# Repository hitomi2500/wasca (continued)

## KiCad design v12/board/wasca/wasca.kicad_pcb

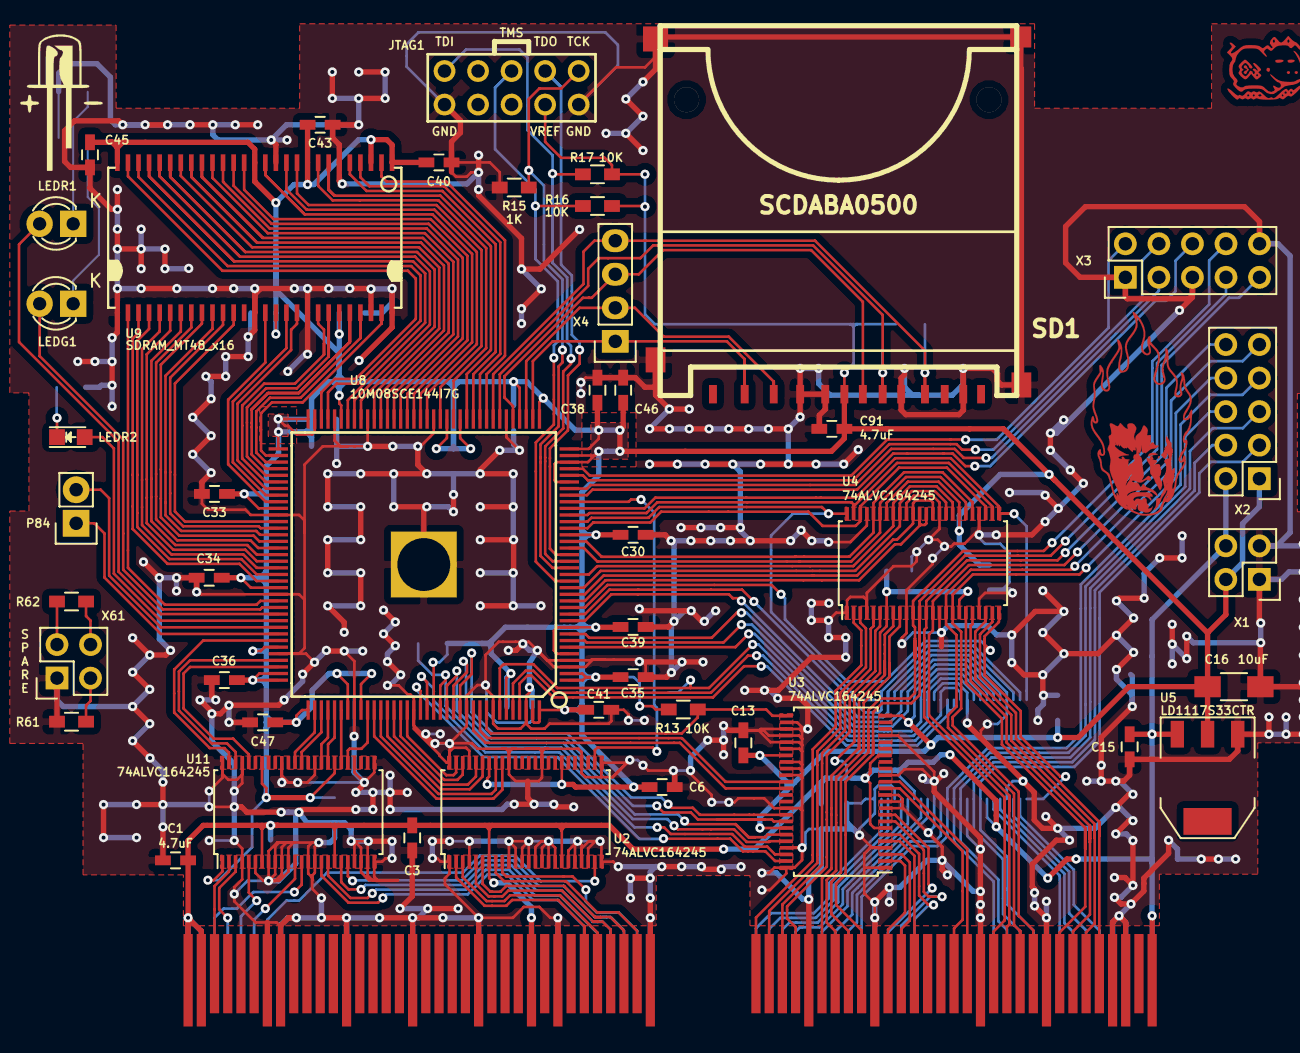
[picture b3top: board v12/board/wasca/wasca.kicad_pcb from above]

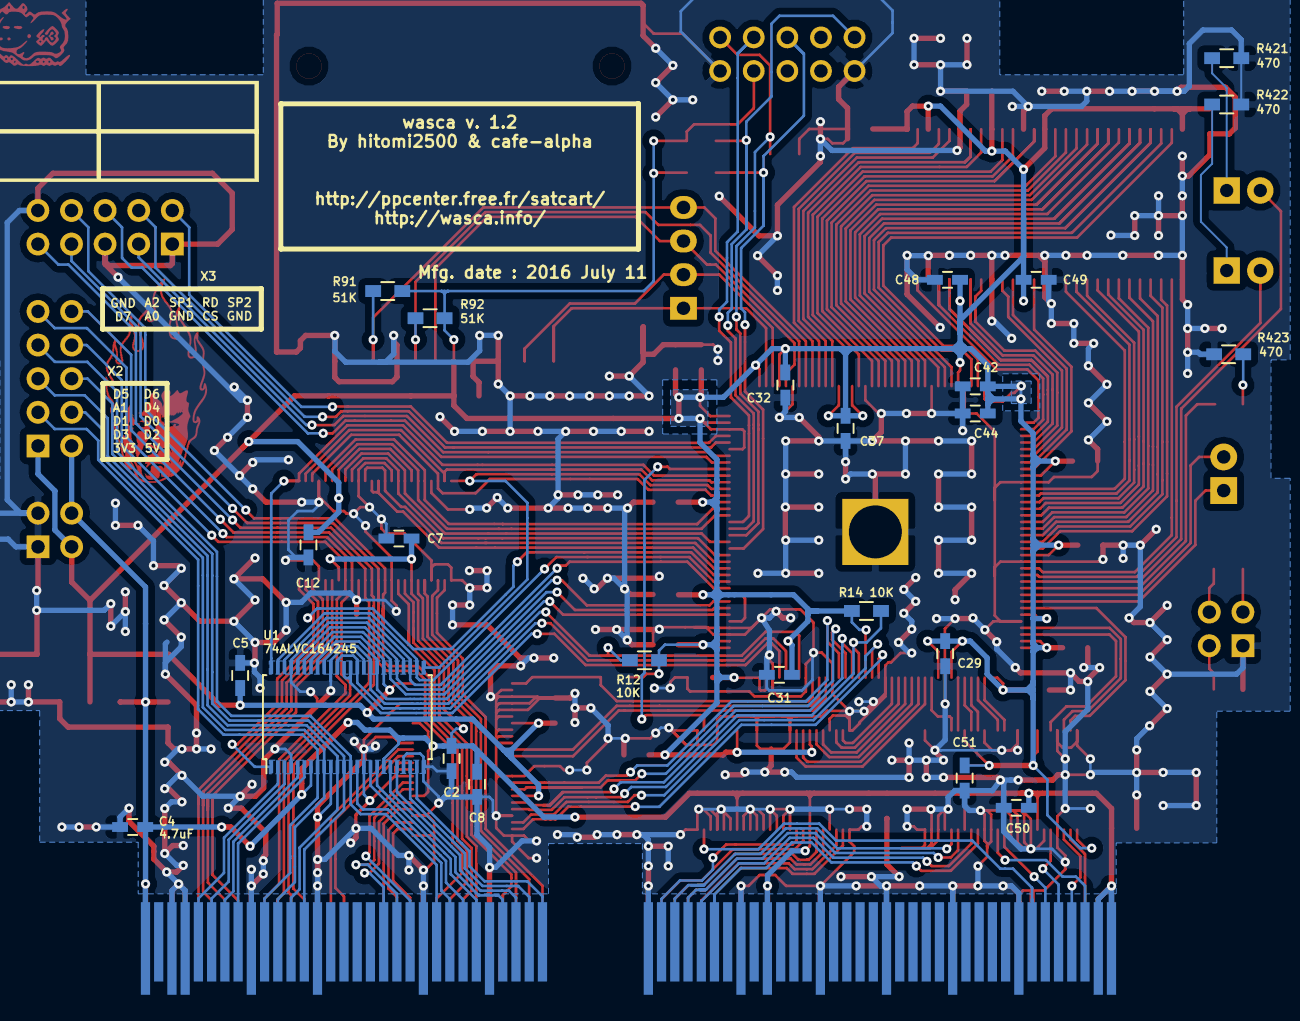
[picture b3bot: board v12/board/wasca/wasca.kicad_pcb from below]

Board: 2 copper layers, 69 parts (24 on the bottom side), 166 nets.

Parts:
C1, C4, C91: 4.7uF; C_0603_HandSoldering
C2, C3, C5, C6, C7, C8, C12, C13, C15, C29, C30, C31, C32, C33, C34, C35, C36, C37, C38, C39, C40, C41, C42, C43, C44, C45, C46, C47, C48, C49, C50, C51: 0.1uF; C_0603_HandSoldering
C16: 10uF; C_1206_HandSoldering
CN1: CARTRIDGE_EDGE_CONNECTOR; CARTRIDGE_EDGE_CONNECTOR2
JTAG1: AVR-JTAG-10; JTAG_Header
LEDG1: LED; LED-3MM
LEDR1: LED; LED-3MM
LEDR2: LED; LED_0805
P84: CONN_01X02; Pin_Header_Straight_1x02
R12, R13, R14, R16, R17: 10K; R_0603_HandSoldering
R15, R61, R62: 1K; R_0603_HandSoldering
R91, R92: 51K; R_0603_HandSoldering
R421, R422, R423: 470; R_0603_HandSoldering
SD1: SD_CARD; sd_socket
U1, U2, U3, U4, U11: 74ALVC164245; TSSOP-48_6.1x12.5mm_Pitch0.5mm
U5: LD1117S33CTR; SOT-223
U8: 10M08SCE144I7G; TQFP144_ALTERA_HANDSOLDERING
U9: SDRAM_MT48_x16; TSOPII54_SDRAM_MT48
X1, X61: CONN_02X02; Pin_Header_Straight_2x02
X2, X3: CONN_02X05; Pin_Header_Straight_2x05
X4: CONN_01X04; Pin_Header_Straight_1x04

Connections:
/+3_3V: C5.1, C6.1, C12.1, C13.1, C16.1, C29.1, C30.1, C31.1, C32.1, C33.1, C34.1, C35.1, C36.1, C37.1, C38.1, C39.1, C40.1, C41.1, C42.1, C43.1, C44.1, C45.1, C46.1, C47.1, C48.1, C49.1, C51.1, C91.1, JTAG1.4, R12.1, R13.1, R14.1, R16.1, R17.1, R91.1, R92.1, SD1.4, U1.31, U1.42, U2.31, U2.42, U3.24, U3.31, U3.42, U4.31, U4.42, U5.2, U8.1, U8.2, U8.5, U8.9, U8.23, U8.31, U8.34, U8.35, U8.36, U8.37, U8.40, U8.49, U8.51, U8.67, U8.71, U8.72, U8.73, U8.82, U8.94, U8.103, U8.107, U8.108, U8.109, U8.115, U8.117, U8.128, U8.139, U8.143, U8.144, U9.1, U9.3, U9.9, U9.14, U9.27, U9.43, U9.49, U11.1, U11.31, U11.42, X1.2, X2.1
/+5V: C1.1, C2.1, C3.1, C4.1, C7.1, C8.1, C15.1, C50.1, CN1.A1, CN1.A2, CN1.A27, CN1.A67, CN1.B1, CN1.B2, CN1.B27, CN1.B67, U1.7, U1.18, U2.7, U2.18, U3.7, U3.18, U4.7, U4.18, U5.3, U11.7, U11.18, X1.4, X2.2
/ABUS_3V_A16: U2.41, U8.120
/ABUS_3V_A17: U2.40, U8.119
/ABUS_3V_A18: U2.43, U8.121
/ABUS_3V_A19: U8.118, U11.29
/ABUS_3V_A20: U2.44, U8.122
/ABUS_3V_A21: U8.114, U11.30
/ABUS_3V_A22: U2.46, U8.123
/ABUS_3V_A23: U8.113, U11.32
/ABUS_3V_A24: U2.47, U8.124
/ABUS_3V_A25: U8.112, U11.33
/ABUS_3V_CS0: U3.40, U8.132
/ABUS_3V_CS1: U3.46, U8.127
/ABUS_3V_CS2: U3.41, U8.131
/ABUS_3V_IRQ: U3.35, U8.135
/ABUS_3V_MUX0: U1.36, U1.37, U8.141
/ABUS_3V_MUX1: U1.35, U1.38, U8.140
/ABUS_3V_MUX2: R12.2, U1.33, U1.40, U8.138
/ABUS_3V_MUX3: U1.32, U1.41, U8.6
/ABUS_3V_MUX4: U4.32, U4.41, U8.17
/ABUS_3V_MUX5: U4.33, U4.40, U8.15
/ABUS_3V_MUX6: U4.35, U4.38, U8.14
/ABUS_3V_MUX7: U4.36, U4.37, U8.13
/ABUS_3V_MUX8: U1.30, U1.43, U8.7
/ABUS_3V_MUX9: U1.29, U1.44, U8.8
/ABUS_3V_MUX10: U1.27, U1.46, U8.10
/ABUS_3V_MUX11: U1.26, U1.47, U8.11
/ABUS_3V_MUX12: U4.26, U4.47, U8.26
/ABUS_3V_MUX13: U4.27, U4.46, U8.24
/ABUS_3V_MUX14: U4.29, U4.44, U8.22
/ABUS_3V_MUX15: U4.30, U4.43, U8.21
/ABUS_3V_MUX_DATA_DIR: U1.1, U4.24, U8.12
/ABUS_3V_MUX_EN1: U1.25, U4.48, U8.25
/ABUS_3V_MUX_EN2: U1.48, U4.25, U8.27
/ABUS_3V_RD: U3.47, U8.126
/ABUS_3V_WAIT: U3.36, U8.134
/ABUS_3V_WR0: U3.43, U8.130
/ABUS_3V_WR1: R14.2, U3.44, U8.129
/ABUS_A0: CN1.B45, U4.12, X3.7
/ABUS_A1: CN1.A45, U1.13, X2.7
/ABUS_A2: CN1.B44, U4.11, X3.8
/ABUS_A3: CN1.B43, U4.9
/ABUS_A4: CN1.B42, U4.8
/ABUS_A5: CN1.B40, U4.6
/ABUS_A6: CN1.B39, U4.5
/ABUS_A7: CN1.B38, U4.3
/ABUS_A8: CN1.A40, U1.19
/ABUS_A9: CN1.A42, U1.17
/ABUS_A10: CN1.A44, U1.14
/ABUS_A11: CN1.A43, U1.16
/ABUS_A12: CN1.A38, U1.22
/ABUS_A13: CN1.A39, U1.20
/ABUS_A14: CN1.B37, U4.2
/ABUS_A15: CN1.A37, U1.23
/ABUS_A16: CN1.B35, U2.8
/ABUS_A17: CN1.A35, U2.9
/ABUS_A18: CN1.B34, U2.6
/ABUS_A19: CN1.A34, U11.20
/ABUS_A20: CN1.B33, U2.5
/ABUS_A21: CN1.A33, U11.19
/ABUS_A22: CN1.B32, U2.3
/ABUS_A23: CN1.A32, U11.17
/ABUS_A24: CN1.B31, U2.2
/ABUS_A25: CN1.A31, U11.16
/ABUS_CS0: CN1.A47, U3.9
/ABUS_CS1: CN1.B48, U3.3
/ABUS_CS2: CN1.A48, U3.8
/ABUS_D0: CN1.A55, U1.12, X2.6
/ABUS_D1: CN1.A56, U1.11, X2.5
/ABUS_D2: CN1.A57, U1.9, X2.4
/ABUS_D3: CN1.A58, U1.8, X2.3
/ABUS_D4: CN1.B58, U4.17, X2.8
/ABUS_D5: CN1.B57, U4.16, X2.9
/ABUS_D6: CN1.B56, U4.14, X2.10
/ABUS_D7: CN1.B55, U4.13, X3.9
/ABUS_D8: CN1.A60, U1.6
/ABUS_D9: CN1.A61, U1.5
/ABUS_D10: CN1.A62, U1.3
/ABUS_D11: CN1.A63, U1.2
/ABUS_D12: CN1.B63, U4.23
/ABUS_D13: CN1.B62, U4.22
/ABUS_D14: CN1.B61, U4.20
/ABUS_D15: CN1.B60, U4.19
/ABUS_IRQ: CN1.B53, U3.14
/ABUS_RD: CN1.B47, U3.2
/ABUS_WAIT: CN1.B52, U3.13
/ABUS_WR0: CN1.A49, U3.6
/ABUS_WR1: CN1.B49, U3.5
/DDR_SPARE1: LEDR2.2, U8.99
/DDR_SPARE2: P84.2, U8.100
/DDR_SPARE3: P84.1, U8.101
/IBCK: CN1.A5, U11.5
/IBCK_3V: U8.106, U11.44
/ILRCK: CN1.A6, U11.12
/ILRCK_3V: U8.110, U11.37
/ISD: CN1.A4, U11.3
/ISD_3V: U8.105, U11.46
/JTAG_TCK: JTAG1.1, R15.1, U8.18
/JTAG_TDI: JTAG1.9, R17.2, U8.19
/JTAG_TDO: JTAG1.3, U8.20
/JTAG_TMS: JTAG1.5, R16.2, U8.16
/LEDG1: LEDG1.2, U8.97
/LEDR1: LEDR1.2, U8.98
/RESET: CN1.A3, U11.13
/RESET_3V: U8.111, U11.36
/SCSPCLK: CN1.A7, U2.23
/SCSPCLK_3V: U2.26, U8.28
/SDR_A0: U8.65, U9.23
/SDR_A1: U8.66, U9.24
/SDR_A2: U8.69, U9.25
/SDR_A3: U8.70, U9.26
/SDR_A4: U8.96, U9.29
/SDR_A5: U8.93, U9.30
/SDR_A6: U8.92, U9.31
/SDR_A7: U8.91, U9.32
/SDR_A8: U8.90, U9.33
/SDR_A9: U8.89, U9.34
/SDR_A10: U8.64, U9.22
/SDR_A11: U8.88, U9.35
/SDR_A12: U8.87, U9.36
/SDR_BA0: U8.61, U9.20
/SDR_BA1: U8.62, U9.21
/SDR_CAS: U8.58, U9.17
/SDR_CKE: U8.86, U9.37
/SDR_CLK: U8.85, U9.38
/SDR_CS: U8.60, U9.19
/SDR_DQ0: U8.45, U9.2
/SDR_DQ1: U8.46, U9.4
/SDR_DQ2: U8.47, U9.5
/SDR_DQ3: U8.48, U9.7
/SDR_DQ4: U8.50, U9.8
/SDR_DQ5: U8.52, U9.10
/SDR_DQ6: U8.54, U9.11
/SDR_DQ7: U8.55, U9.13
/SDR_DQ8: U8.81, U9.42
/SDR_DQ9: U8.80, U9.44
/SDR_DQ10: U8.79, U9.45
/SDR_DQ11: U8.78, U9.47
/SDR_DQ12: U8.77, U9.48
/SDR_DQ13: U8.76, U9.50
/SDR_DQ14: U8.75, U9.51
/SDR_DQ15: U8.74, U9.53
/SDR_DQMH: U8.84, U9.39
/SDR_DQML: U8.56, U9.15
/SDR_RAS: U8.59, U9.18
/SDR_WE: U8.57, U9.16
/SD_CLK: SD1.5, U8.41, X4.3
/SD_CS: SD1.1, U8.38, X4.1
/SD_DIN: SD1.2, U8.39, X4.2
/SD_DOUT: R91.2, SD1.7, U8.44, X4.4
/SSEL: CN1.B3, U11.2
/SSEL_3V: U8.102, U11.47
/USB_CS: U8.30, X3.3
/USB_RD: U8.32, X3.4
/USB_SPARE1: U8.29, X3.6
/USB_SPARE2: U8.33, X3.2
/WAIT_ENABLE: R13.2, U3.25, U8.136
GND: C1.2, C2.2, C3.2, C4.2, C5.2, C6.2, C7.2, C8.2, C12.2, C13.2, C15.2, C16.2, C29.2, C30.2, C31.2, C32.2, C33.2, C34.2, C35.2, C36.2, C37.2, C38.2, C39.2, C40.2, C41.2, C42.2, C43.2, C44.2, C45.2, C46.2, C47.2, C48.2, C49.2, C50.2, C51.2, C91.2, CN1.A8, CN1.A13, CN1.A18, CN1.A23, CN1.A29, CN1.A36, CN1.A41, CN1.A46, CN1.A54, CN1.A59, CN1.A64, CN1.A65, CN1.B7, CN1.B8, CN1.B13, CN1.B18, CN1.B23, CN1.B29, CN1.B36, CN1.B41, CN1.B46, CN1.B54, CN1.B59, CN1.B64, CN1.B65, JTAG1.2, JTAG1.10, R15.2, R61.1, R421.2, R422.2, R423.2, SD1.3, SD1.6, SD1.12, SD1.13, SD1.14, SD1.15, SD1.16, SD1.17, U1.4, U1.10, U1.15, U1.21, U1.24, U1.28, U1.34, U1.39, U1.45, U2.1, U2.4, U2.10, U2.11, U2.12, U2.13, U2.14, U2.15, U2.16, U2.17, U2.19, U2.20, U2.21, U2.22, U2.24, U2.25, U2.28, U2.34, U2.39, U2.45, U2.48, U3.1, U3.4, U3.10, U3.11, U3.12, U3.15, U3.21, U3.26, U3.27, U3.28, U3.29, U3.30, U3.32, U3.33, U3.34, U3.39, U3.45, U3.48, U4.1, U4.4, U4.10, U4.15, U4.21, U4.28, U4.34, U4.39, U4.45, U5.1, U8.3, U8.4, U8.42, U8.53, U8.63, U8.68, U8.83, U8.95, U8.104, U8.116, U8.125, U8.133, U8.137, U8.142, U8.145, U9.6, U9.12, U9.28, U9.41, U9.46, U9.52, U9.54, U11.4, U11.6, U11.8, U11.9, U11.10, U11.11, U11.14, U11.15, U11.21, U11.22, U11.23, U11.24, U11.25, U11.28, U11.34, U11.39, U11.45, U11.48, X1.1, X1.3, X3.1, X3.5, X3.10, X61.1
unnamed: LEDG1.1, R422.1
unnamed: LEDR1.1, R421.1
unnamed: LEDR2.1, R423.1
unnamed: R61.2, X61.3
unnamed: R62.1, X61.2
unnamed: R62.2, X61.4
unnamed: R92.2, SD1.10, U8.43

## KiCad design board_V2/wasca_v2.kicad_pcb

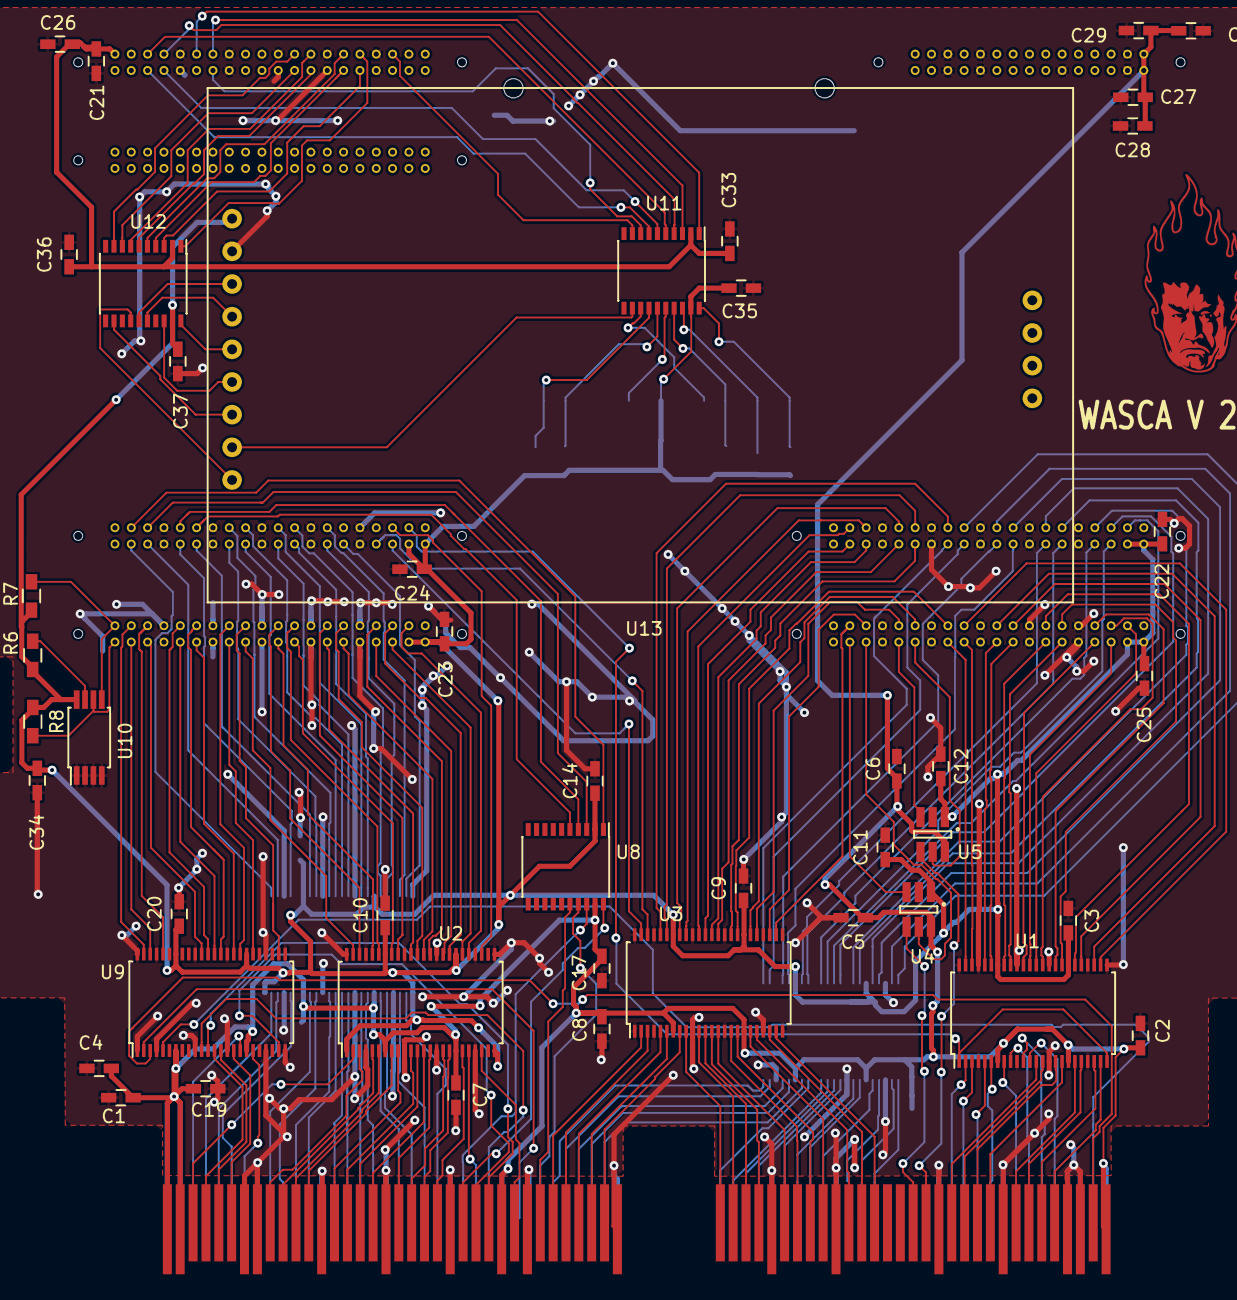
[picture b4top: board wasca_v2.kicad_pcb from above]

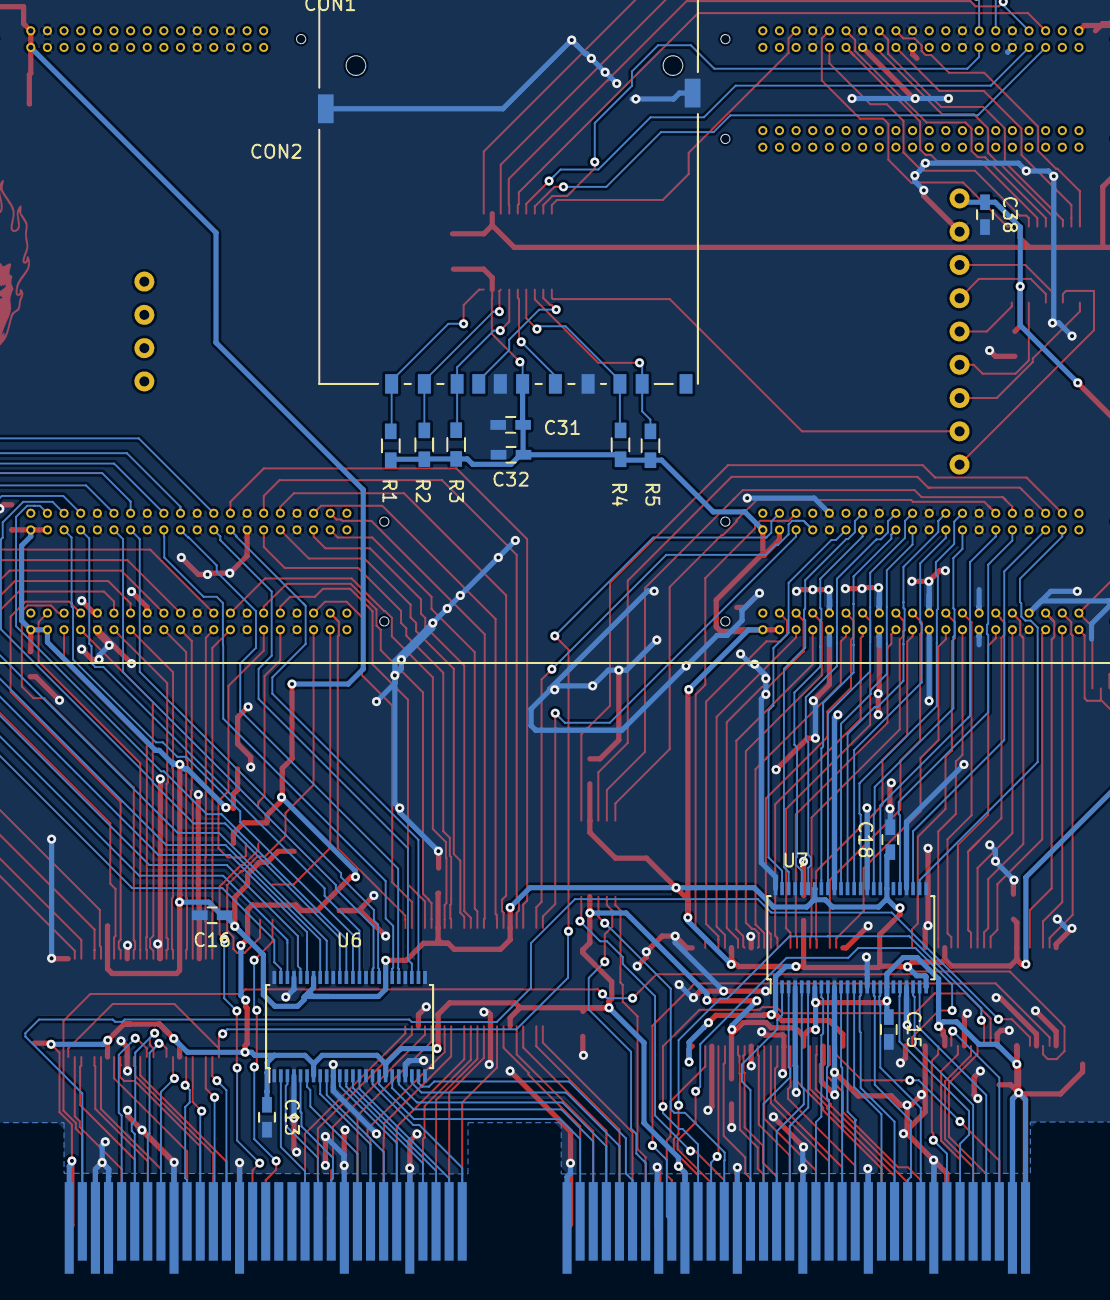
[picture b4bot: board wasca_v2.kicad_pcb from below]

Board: 2 copper layers, 62 parts (16 on the bottom side), 230 nets.

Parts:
C1, C26, C28, C30: 10uF; C_0603_HandSoldering
C2, C3, C4, C5, C6, C7, C8, C9, C10, C11, C12, C13, C14, C15, C16, C17, C18, C19, C20, C21, C22, C23, C24, C25, C27, C29, C32, C33, C34, C35, C36, C37, C38: 0.1uF; C_0603_HandSoldering
C31: 1uF; C_0603_HandSoldering
CN1: CARTRIDGE_EDGE_CONNECTOR; CARTRIDGE_EDGE_CONNECTOR2
CON1: SnickerDoodle
CON2: SD_Card; SD_Card_Receptacle
R1, R2, R3, R4, R5: 50K; R_0603_HandSoldering
R6: 0; R_0603_HandSoldering
R7, R8: 10K; R_0603_HandSoldering
U1, U2, U3, U6, U7, U9: 74ALVC164245; TSSOP-48_6.1x12.5mm_Pitch0.5mm
U4, U5: 74LVC1T45GW,125; SOT-23-6_Handsoldering
U8, U11, U12: TXS0108EPWR; SSOP-20_4.4x6.5mm_Pitch0.65mm
U10: M24C04-WDW6TP; TSSOP-8_4.4x3mm_Pitch0.65mm
U13: ILI9341_LCD_Breakout

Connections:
/+1_8V: C21.1, C26.1, C33.1, C36.1, CON1.B1, U11.2, U12.2
/+3_3V: C3.1, C9.1, C10.1, C11.1, C12.1, C14.1, C16.1, C18.1, C20.1, C22.1, C23.1, C24.1, C25.1, C31.1, C32.1, C34.1, C35.1, C37.1, C38.1, CON1.C1, CON1.C3, CON1.D1, CON1.D3, CON1.E1, CON1.E3, CON1.F1, CON1.F3, CON2.4, R1.1, R2.1, R3.1, R4.1, R5.1, R6.1, R7.1, R8.1, U1.31, U1.42, U2.1, U2.24, U2.31, U2.42, U3.31, U3.42, U4.1, U5.1, U6.31, U6.42, U7.1, U7.24, U7.31, U7.42, U8.2, U9.31, U9.42, U10.8, U11.19, U12.19, U13.1
/+5V: C1.1, C2.1, C4.1, C5.1, C6.1, C7.1, C8.1, C13.1, C15.1, C17.1, C19.1, C27.1, C28.1, C29.1, C30.1, CN1.A1, CN1.A2, CN1.A27, CN1.A67, CN1.B1, CN1.B2, CN1.B27, CN1.B67, CON1.A29, CON1.A30, U1.7, U1.18, U2.7, U2.18, U3.7, U3.18, U4.6, U5.6, U6.7, U6.18, U7.7, U7.18, U8.19, U9.7, U9.18
/ABUS_A0: CN1.B45, U3.19
/ABUS_A0_3V: CON1.E30, U3.30
/ABUS_A1: CN1.A45, U6.6
/ABUS_A1_3V: CON1.F14, U6.43
/ABUS_A2: CN1.B44, U3.17
/ABUS_A2_3V: CON1.E26, U3.32
/ABUS_A3: CN1.B43, U3.16
/ABUS_A3_3V: CON1.F29, U3.33
/ABUS_A4: CN1.B42, U3.14
/ABUS_A4_3V: CON1.F31, U3.35
/ABUS_A5: CN1.B40, U3.13
/ABUS_A5_3V: CON1.F35, U3.36
/ABUS_A6: CN1.B39, U3.12
/ABUS_A6_3V: CON1.F37, U3.37
/ABUS_A7: CN1.B38, U3.11
/ABUS_A7_3V: CON1.F38, U3.38
/ABUS_A8: CN1.A40, U6.12
/ABUS_A8_3V: CON1.F4, U6.37
/ABUS_A9: CN1.A42, U6.11
/ABUS_A9_3V: CON1.F6, U6.38
/ABUS_A10: CN1.A44, U6.8
/ABUS_A10_3V: CON1.F12, U6.41
/ABUS_A11: CN1.A43, U6.9
/ABUS_A11_3V: CON1.F8, U6.40
/ABUS_A12: CN1.A38, U6.14
/ABUS_A12_3V: CON1.F7, U6.35
/ABUS_A13: CN1.A39, U6.13
/ABUS_A13_3V: CON1.F5, U6.36
/ABUS_A14: CN1.B37, U3.9
/ABUS_A14_3V: CON1.F36, U3.40
/ABUS_A15: CN1.A37, U6.16
/ABUS_A15_3V: CON1.F11, U6.33
/ABUS_A16: CN1.B35, U3.8
/ABUS_A16_3V: CON1.F32, U3.41
/ABUS_A17: CN1.A35, U6.17
/ABUS_A17_3V: CON1.F13, U6.32
/ABUS_A18: CN1.B34, U3.6
/ABUS_A18_3V: CON1.F30, U3.43
/ABUS_A19: CN1.A34, U6.19
/ABUS_A19_3V: CON1.F17, U6.30
/ABUS_A20: CN1.B33, U3.5
/ABUS_A20_3V: CON1.F26, U3.44
/ABUS_A21: CN1.A33, U6.20
/ABUS_A21_3V: CON1.F19, U6.29
/ABUS_A22: CN1.B32, U3.3
/ABUS_A22_3V: CON1.D7, U3.46
/ABUS_A23: CN1.A32, U6.22
/ABUS_A23_3V: CON1.F23, U6.27
/ABUS_A24: CN1.B31, U3.2
/ABUS_A24_3V: CON1.D5, U3.47
/ABUS_A25: CN1.A31, U6.23
/ABUS_A25_3V: CON1.F25, U6.26
/ABUS_CS0: CN1.A47, U6.5
/ABUS_CS0_3V: CON1.F18, U6.44
/ABUS_CS1: CN1.B48, U3.22
/ABUS_CS1_3V: CON1.E36, U3.27
/ABUS_CS2: CN1.A48, U6.3
/ABUS_CS2_3V: CON1.F20, U6.46
/ABUS_D0: CN1.A55, U1.2
/ABUS_D0_3V: CON1.E25, U1.47
/ABUS_D1: CN1.A56, U1.3
/ABUS_D1_3V: CON1.E23, U1.46
/ABUS_D2: CN1.A57, U1.5
/ABUS_D2_3V: CON1.E19, U1.44
/ABUS_D3: CN1.A58, U1.6
/ABUS_D3_3V: CON1.E17, U1.43
/ABUS_D4: CN1.B58, U1.17
/ABUS_D4_3V: CON1.E12, U1.32
/ABUS_D5: CN1.B57, U1.16
/ABUS_D5_3V: CON1.E8, U1.33
/ABUS_D6: CN1.B56, U1.14
/ABUS_D6_3V: CON1.E6, U1.35
/ABUS_D7: CN1.B55, U1.13
/ABUS_D7_3V: CON1.E4, U1.36
/ABUS_D8: CN1.A60, U1.8
/ABUS_D8_3V: CON1.E13, U1.41
/ABUS_D9: CN1.A61, U1.9
/ABUS_D9_3V: CON1.E11, U1.40
/ABUS_D10: CN1.A62, U1.11
/ABUS_D10_3V: CON1.E7, U1.38
/ABUS_D11: CN1.A63, U1.12
/ABUS_D11_3V: CON1.E5, U1.37
/ABUS_D12: CN1.B63, U1.23
/ABUS_D12_3V: CON1.E24, U1.26
/ABUS_D13: CN1.B62, U1.22
/ABUS_D13_3V: CON1.E20, U1.27
/ABUS_D14: CN1.B61, U1.20
/ABUS_D14_3V: CON1.E18, U1.29
/ABUS_D15: CN1.B60, U1.19
/ABUS_D15_3V: CON1.E14, U1.30
/ABUS_DATA_DIR: CON1.D4, U1.1, U1.24
/ABUS_IRQ: CN1.B53, U5.4
/ABUS_IRQ_3V: CON1.E31, U5.3
/ABUS_IRQ_DIR: CON1.E29, U5.5
/ABUS_RD: CN1.B47, U3.20
/ABUS_RD_3V: CON1.E32, U3.29
/ABUS_WAIT: CN1.B52, U4.4
/ABUS_WAIT_3V: CON1.E37, U4.3
/ABUS_WAIT_DIR: CON1.E35, U4.5
/ABUS_WR0: CN1.A49, U6.2
/ABUS_WR0_3V: CON1.F24, U6.47
/ABUS_WR1: CN1.B49, U3.23
/ABUS_WR1_3V: CON1.E38, U3.26
/COPRO_RST: CN1.A66, U9.5
/COPRO_RST_3V: CON1.C36, U9.44
/CRTG0: CN1.A30, U8.17
/CRTG0_3V: CON1.D32, U8.4
/CRTG1: CN1.B30, U8.16
/CRTG1_3V: CON1.D30, U8.5
/DBCK: CN1.B5, U9.14
/DBCK_3V: CON1.C30, U9.35
/DLRCLK: CN1.B6, U9.16
/DLRCLK_3V: CON1.C29, U9.33
/DOTCLK: CN1.A28, U9.2
/DOTCLK_3V: CON1.C38, U9.47
/DSD: CN1.B4, U9.13
/DSD_3V: CON1.C31, U9.36
/EXBG0: CN1.A9, U7.17
/EXBG0_3V: CON1.D29, U7.32
/EXBG1: CN1.B9, U2.3
/EXBG1_3V: CON1.C20, U2.46
/EXBG2: CN1.A10, U7.16
/EXBG2_3V: CON1.D25, U7.33
/EXBG3: CN1.B10, U2.5
/EXBG3_3V: CON1.C19, U2.44
/EXBG4: CN1.A11, U7.14
/EXBG4_3V: CON1.D26, U7.35
/EXBG5: CN1.B11, U2.6
/EXBG5_3V: CON1.C18, U2.43
/EXBG6: CN1.A12, U7.13
/EXBG6_3V: CON1.D23, U7.36
/EXBG7: CN1.B12, U2.8
/EXBG7_3V: CON1.C17, U2.41
/EXBG8: CN1.A14, U7.12
/EXBG8_3V: CON1.D24, U7.37
/EXBG9: CN1.B14, U2.9
/EXBG9_3V: CON1.C14, U2.40
/EXBG10: CN1.A15, U7.11
/EXBG10_3V: CON1.D19, U7.38
/EXBG11: CN1.B15, U2.11
/EXBG11_3V: CON1.C13, U2.38
/EXBG12: CN1.A16, U7.9
/EXBG12_3V: CON1.D20, U7.40
/EXBG13: CN1.B16, U2.12
/EXBG13_3V: CON1.C12, U2.37
/EXBG14: CN1.A17, U7.8
/EXBG14_3V: CON1.D17, U7.41
/EXBG15: CN1.B17, U2.13
/EXBG15_3V: CON1.C11, U2.36
/EXBG16: CN1.A19, U7.6
/EXBG16_3V: CON1.D18, U7.43
/EXBG17: CN1.B19, U2.14
/EXBG17_3V: CON1.C8, U2.35
/EXBG18: CN1.A20, U7.5
/EXBG18_3V: CON1.D13, U7.44
/EXBG19: CN1.B20, U2.16
/EXBG19_3V: CON1.C7, U2.33
/EXBG20: CN1.A21, U7.3
/EXBG20_3V: CON1.D14, U7.46
/EXBG21: CN1.B21, U2.17
/EXBG21_3V: CON1.C6, U2.32
/EXBG22: CN1.A22, U7.2
/EXBG22_3V: CON1.D11, U7.47
/EXBG23: CN1.B22, U2.19
/EXBG23_3V: CON1.C5, U2.30
/EXLAT: CN1.A25, U2.20
/EXLAT_3V: CON1.C4, U2.29
/EXON: CN1.A24, U8.18
/EXON_3V: CON1.D36, U8.3
/EXSL: CN1.B25, U9.23
/EXSL_3V: CON1.C24, U9.26
/EXSYNC: CN1.B28, U2.22
/EXSYNC_3V: CON1.D6, U2.27
/HSYNC: CN1.A26, U9.11
/HSYNC_3V: CON1.C35, U9.38
/IBCK: CN1.A5, U7.22
/IBCK_3V: CON1.D35, U7.27
/ILRCK: CN1.A6, U7.20
/ILRCK_3V: CON1.D31, U7.29
/ISD: CN1.A4, U7.23
/ISD_3V: CON1.D37, U7.26
/LCD_DC: U12.20, U13.5
/LCD_DC_1_8V: CON1.B32, U12.3
/LCD_LED: U11.12, U13.8
/LCD_LED_1_8V: CON1.B35, U11.9
/LCD_RESET: U12.16, U13.4
/LCD_RESET_1_8V: CON1.B30, U12.4
/MCLK: CN1.B66, U9.3
/MCLK_3V: CON1.C37, U9.46
/MPEGON: CN1.B24, U8.20
/MPEGON_3V: CON1.D38, U8.1
/RESET: CN1.A3, U9.17
/RESET_3V: CON1.C26, U9.32
/SCSPCLK: CN1.A7, U9.19
/SCSPCLK_3V: CON1.C25, U9.30
/SD_CD/DAT3: CON2.1, R2.2, U11.18
/SD_CD/DAT3_1_8V: CON1.B13, U11.3
/SD_CLK: CON2.5, U11.16
/SD_CLK_1_8V: CON1.B5, U11.5
/SD_CMD: CON2.2, R3.2, U11.17
/SD_CMD_1_8V: CON1.B7, U11.4
/SD_DAT0: CON2.7, R4.2, U11.15
/SD_DAT0_1_8V: CON1.B8, U11.6
/SD_DAT1: CON2.8, R5.2, U11.14
/SD_DAT1_1_8V: CON1.B6, U11.7
/SD_DAT2: CON2.9, R1.2, U11.20
/SD_DAT2_1_8V: CON1.B11, U11.1
/SD_WP: CON2.10, U11.13
/SD_WP_1_8V: CON1.B14, U11.8
/SPI_CS0: U12.15, U13.3
/SPI_CS0_1_8V: CON1.B26, U12.6
/SPI_CS1_1_8V: CON1.B24, U12.8
/SPI_CS2_1_8V: CON1.B29, U12.5
/SPI_MISO: U12.14, U13.9
/SPI_MISO_1_8V: CON1.B25, U12.7
/SPI_MOSI: U12.18, U13.6
/SPI_MOSI_1_8V: CON1.B31, U12.1
/SPI_SCK: U12.12, U13.7
/SPI_SCK_1_8V: CON1.B23, U12.9
/SSEL: CN1.B3, U2.2
/SSEL_3V: CON1.C23, U2.47
/VSYNC: CN1.B26, U9.12
/VSYNC_3V: CON1.C32, U9.37
GND: C1.2, C2.2, C3.2, C4.2, C5.2, C6.2, C7.2, C8.2, C9.2, C10.2, C11.2, C12.2, C13.2, C14.2, C15.2, C16.2, C17.2, C18.2, C19.2, C20.2, C21.2, C22.2, C23.2, C24.2, C25.2, C26.2, C27.2, C28.2, C29.2, C30.2, C31.2, C32.2, C33.2, C34.2, C35.2, C36.2, C37.2, C38.2, CN1.A8, CN1.A13, CN1.A18, CN1.A23, CN1.A29, CN1.A36, CN1.A41, CN1.A46, CN1.A54, CN1.A59, CN1.A64, CN1.A65, CN1.B7, CN1.B8, CN1.B13, CN1.B18, CN1.B23, CN1.B29, CN1.B36, CN1.B41, CN1.B46, CN1.B54, CN1.B59, CN1.B64, CN1.B65, CON1.A5, CON1.A6, CON1.A9, CON1.A10, CON1.A20, CON1.A27, CON1.A28, CON1.B9, CON1.B10, CON1.B15, CON1.B16, CON1.B21, CON1.B22, CON1.B27, CON1.B28, CON1.B33, CON1.B34, CON1.C9, CON1.C10, CON1.C15, CON1.C16, CON1.C21, CON1.C22, CON1.C27, CON1.C28, CON1.C33, CON1.C34, CON1.D9, CON1.D10, CON1.D15, CON1.D16, CON1.D21, CON1.D22, CON1.D27, CON1.D28, CON1.D33, CON1.D34, CON1.E9, CON1.E10, CON1.E15, CON1.E16, CON1.E21, CON1.E22, CON1.E27, CON1.E28, CON1.E33, CON1.E34, CON1.F9, CON1.F10, CON1.F15, CON1.F16, CON1.F21, CON1.F22, CON1.F27, CON1.F28, CON1.F33, CON1.F34, CON2.3, CON2.6, CON2.12, CON2.13, U1.4, U1.10, U1.15, U1.21, U1.25, U1.28, U1.34, U1.39, U1.45, U1.48, U2.4, U2.10, U2.15, U2.21, U2.25, U2.28, U2.34, U2.39, U2.45, U2.48, U3.1, U3.4, U3.10, U3.15, U3.21, U3.24, U3.25, U3.28, U3.34, U3.39, U3.45, U3.48, U4.2, U5.2, U6.1, U6.4, U6.10, U6.15, U6.21, U6.24, U6.25, U6.28, U6.34, U6.39, U6.45, U6.48, U7.4, U7.10, U7.15, U7.21, U7.25, U7.28, U7.34, U7.39, U7.45, U7.48, U9.1, U9.4, U9.10, U9.15, U9.21, U9.24, U9.25, U9.28, U9.34, U9.39, U9.45, U9.48, U10.1, U10.2, U10.3, U10.4, U13.2
unnamed: CON1.C39, R8.2, U10.6
unnamed: CON1.C40, R7.2, U10.5
unnamed: R6.2, U10.7

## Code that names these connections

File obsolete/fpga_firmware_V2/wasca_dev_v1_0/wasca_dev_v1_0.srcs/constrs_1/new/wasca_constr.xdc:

set_property PACKAGE_PIN L14 [get_ports {abus_address[24]}]
set_property PACKAGE_PIN L15 [get_ports {abus_address[22]}]
set_property PACKAGE_PIN U20 [get_ports {abus_address[25]}]
set_property PACKAGE_PIN T20 [get_ports {abus_address[23]}]
set_property PACKAGE_PIN V18 [get_ports {abus_address[21]}]
set_property PACKAGE_PIN V17 [get_ports {abus_address[19]}]
set_property PACKAGE_PIN R18 [get_ports {abus_address[17]}]
set_property PACKAGE_PIN T17 [get_ports {abus_address[15]}]
set_property PACKAGE_PIN P19 [get_ports {abus_address[14]}]
set_property PACKAGE_PIN N18 [get_ports {abus_address[7]}]
set_property PACKAGE_PIN Y19 [get_ports {abus_address[18]}]
set_property PACKAGE_PIN Y18 [get_ports {abus_address[16]}]
set_property IOSTANDARD LVCMOS33 [get_ports {abus_address[25]}]
set_property IOSTANDARD LVCMOS33 [get_ports {abus_address[24]}]
set_property IOSTANDARD LVCMOS33 [get_ports {abus_address[23]}]
set_property IOSTANDARD LVCMOS33 [get_ports {abus_address[22]}]
set_property IOSTANDARD LVCMOS33 [get_ports {abus_address[21]}]
set_property IOSTANDARD LVCMOS33 [get_ports {abus_address[20]}]
set_property IOSTANDARD LVCMOS33 [get_ports {abus_address[19]}]
set_property IOSTANDARD LVCMOS33 [get_ports {abus_address[18]}]
set_property IOSTANDARD LVCMOS33 [get_ports {abus_address[17]}]
set_property IOSTANDARD LVCMOS33 [get_ports {abus_address[16]}]
set_property IOSTANDARD LVCMOS33 [get_ports {abus_address[15]}]
set_property IOSTANDARD LVCMOS33 [get_ports {abus_address[14]}]
set_property IOSTANDARD LVCMOS33 [get_ports {abus_address[13]}]
set_property IOSTANDARD LVCMOS33 [get_ports {abus_address[12]}]
set_property IOSTANDARD LVCMOS33 [get_ports {abus_address[11]}]
set_property IOSTANDARD LVCMOS33 [get_ports {abus_address[10]}]
set_property IOSTANDARD LVCMOS33 [get_ports {abus_address[9]}]
set_property IOSTANDARD LVCMOS33 [get_ports {abus_address[8]}]
set_property IOSTANDARD LVCMOS33 [get_ports {abus_address[7]}]
set_property IOSTANDARD LVCMOS33 [get_ports {abus_address[6]}]
set_property IOSTANDARD LVCMOS33 [get_ports {abus_address[5]}]
set_property IOSTANDARD LVCMOS33 [get_ports {abus_address[4]}]
set_property IOSTANDARD LVCMOS33 [get_ports {abus_address[3]}]
set_property IOSTANDARD LVCMOS33 [get_ports {abus_address[2]}]
set_property IOSTANDARD LVCMOS33 [get_ports {abus_address[1]}]
set_property IOSTANDARD LVCMOS33 [get_ports {abus_address[0]}]
set_property IOSTANDARD LVCMOS33 [get_ports abus_reset]
set_property PACKAGE_PIN W19 [get_ports {abus_chipselect[0]}]
set_property PACKAGE_PIN W18 [get_ports {abus_chipselect[2]}]
set_property PACKAGE_PIN W16 [get_ports {abus_write[0]}]
set_property PACKAGE_PIN V16 [get_ports {abus_address[20]}]
set_property PACKAGE_PIN R17 [get_ports {abus_address[10]}]
set_property PACKAGE_PIN R16 [get_ports {abus_address[1]}]
set_property PACKAGE_PIN P16 [get_ports {abus_address[9]}]
set_property PACKAGE_PIN P15 [get_ports {abus_address[11]}]
set_property PACKAGE_PIN P20 [get_ports {abus_address[6]}]
set_property PACKAGE_PIN N20 [get_ports {abus_address[5]}]
set_property PACKAGE_PIN W20 [get_ports {abus_address[4]}]
set_property PACKAGE_PIN V20 [get_ports {abus_address[3]}]
set_property PACKAGE_PIN P18 [get_ports {abus_address[12]}]
set_property PACKAGE_PIN N17 [get_ports {abus_address[13]}]
set_property PACKAGE_PIN T10 [get_ports {data_to_and_from_pins[10]}]
set_property PACKAGE_PIN T11 [get_ports {data_to_and_from_pins[11]}]
set_property PACKAGE_PIN R14 [get_ports {data_to_and_from_pins[8]}]
set_property PACKAGE_PIN P14 [get_ports {data_to_and_from_pins[9]}]
set_property PACKAGE_PIN V13 [get_ports {data_to_and_from_pins[2]}]
set_property PACKAGE_PIN U13 [get_ports {data_to_and_from_pins[3]}]
set_property PACKAGE_PIN U17 [get_ports {data_to_and_from_pins[0]}]
set_property PACKAGE_PIN T16 [get_ports {data_to_and_from_pins[1]}]
set_property PACKAGE_PIN Y14 [get_ports {abus_irq[0]}]
set_property PACKAGE_PIN U15 [get_ports abus_wait]
set_property PACKAGE_PIN U19 [get_ports {abus_chipselect[1]}]
set_property PACKAGE_PIN U18 [get_ports {abus_write[1]}]
set_property PACKAGE_PIN W15 [get_ports {abus_address[0]}]
set_property PACKAGE_PIN V15 [get_ports abus_read]
set_property PACKAGE_PIN Y17 [get_ports {data_to_and_from_pins[12]}]
set_property PACKAGE_PIN Y16 [get_ports {abus_address[2]}]
set_property PACKAGE_PIN T15 [get_ports {data_to_and_from_pins[14]}]
set_property PACKAGE_PIN T14 [get_ports {data_to_and_from_pins[13]}]
set_property PACKAGE_PIN W13 [get_ports {data_to_and_from_pins[4]}]
set_property PACKAGE_PIN V12 [get_ports {data_to_and_from_pins[15]}]
set_property PACKAGE_PIN U12 [get_ports {data_to_and_from_pins[6]}]
set_property PACKAGE_PIN T12 [get_ports {data_to_and_from_pins[5]}]
set_property PACKAGE_PIN R19 [get_ports {abus_address[8]}]
set_property PACKAGE_PIN T19 [get_ports {data_to_and_from_pins[7]}]
set_property PACKAGE_PIN G19 [get_ports abus_reset]

set_property IOSTANDARD LVCMOS33 [get_ports abus_data_dir]
set_property PACKAGE_PIN J15 [get_ports abus_data_dir]

set_property IOSTANDARD LVCMOS33 [get_ports abus_irq_dir]
set_property PACKAGE_PIN W14 [get_ports abus_irq_dir]
set_property IOSTANDARD LVCMOS33 [get_ports abus_wait_dir]
set_property PACKAGE_PIN U14 [get_ports abus_wait_dir]

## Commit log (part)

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2015-12-01 Status update
2016-05-27 Wasca evolution as a snickerdoodle baseboard, see https://github.com/krtkl/snickerdoodle-manual
2016-05-31 Pin swapping (incomplete)
2016-06-05 Route done
2016-07-14 Minor changes to boards
    - Added chip orientation information for 3V3 buffers and MAX10
    footprints
    - Added gerber files
2017-03-03 Zynq base firmware added (not tested on hardware yet).
2017-03-16 Minor HDL updates
2017-03-17 ABus interwork in progress
2020-08-13 Migrating from 15.0 to 15.1, debug signaltap updated, .gitignore added
2020-08-17 SH-2 software update to v. 6.363
2020-08-18 Syntax errors fixed
2020-08-18 Minimalistic testbench with a reference sdram controller core from https://github.com/stffrdhrn/sdram-controller
2020-08-19 Bridge core plugged into Qsys. First direct test negative, SH-2 cannot see the bootcode yet. More debugging to follow.
2020-08-20 Bridge core debugging in Qsys. Avalon almost works, some bus width issues are not yet fixed
2020-08-21 Holy crap!
2020-08-22 It works! 16 bit and 32 bit accesses are working without errors.
2020-08-26 Adding a sniffer core
2020-08-28 RAM 1M mirroring
2020-08-29 Further timing optimization. Refresh latency is back to 8 cycles. Glitches in KOF'96 changed, but not gone.
2020-08-30 Removing minimap mem
2020-09-01 New counter & sniffer with filter & FIFO
2020-09-04 Onchip flash removed from qsys - removing artifacts.
2020-09-08 Just some quartus's junk
2020-09-14 Wascaloader now successfully boots from SD card.
2020-09-15 Gitignore update
2020-09-19 Writing works, but syncing can't keep up with writing, so there are skips.
2020-09-27 Removing obsolete cores
2020-09-28 Embedding buffered spi, some inferring gone wrong
2020-10-03 SPI core works correctly in transmit mode (receive not tested yet). A simple test is added at the start of the main.
2020-10-06 Updating sniffer core (making it block-wise)
2020-10-07 Sniffer FIFO now sniffs correctly, but the syncing doesn't work yet (formatting does not erase everything)
2020-10-11 Loading KoF'95 and Ultraman roms from SD
2020-10-13 Mapper register set works. Fixed incorrect disable value for waitrequest and interrupt
2020-10-14 Ultraman ROM support
2020-10-25 Lazy save integrity check (disabled)
2020-11-09 Moving V2 to the "obsolete" folder to mark its obsolescence
2020-12-06 Board 1.4 (not finished yet)
2020-12-07 Reroute of swapped pins
2020-12-10 Further routing
2020-12-10 STM32 pinout update
2020-12-13 Recompiling FPGA for 10M08SCE144C8G part
2020-12-18 Switching to LVCMOS from LVTTL
2020-12-19 Old unused SDRAM debug project removed
2020-12-19 Heartbeat core added. Sync pin added to burrered SPI core. Uart disconnected from outputs (but is still enabled because of Nios)
2020-12-19 Moving software to 2018.1. All UP SD card functions commented, because there is no UP SD core anymore.
2021-01-21 Added buffered log output to STM32 (which shall then send the logs to PC via USB) Can now select between log output to STM32 or UART Small changes regarding boot ROM selection
2021-01-30 Moving to 60MHz clock from STM32
2021-01-31 Improvements in log output to UART & minor changes regarding boot ROM loading. + allow to change UART baud rate from Nios.
2021-01-31 Input clock switch from 60Mhz to 8 MHz
2021-02-05 Removing v12 folder before merging (will be re-added as a branch to hitomi2500/wasca after merging)
2021-02-05 Remove local Middlewares part of the STM32 library
2021-02-05 Board v1.2
2021-02-06 Timing constraints update (external clock set to 8MHz)
2021-02-10 On MAX 10 startup, output STM32 firmware build date to UART
2021-02-10 Add the ability to build or flash STM32 firmware from mk.bat
2021-02-11 Add settings files for OpenOCD
2021-02-11 Check boot ROM data integrity, and re-request it if necessary
2021-02-12 Improved MAX 10 LED blinker, to get an idea where execution is freezing.
2021-02-13 A bit smarter data integrity check during SPI transfer (but still not working well)
2021-02-20 Output one test log message to UART every second from STM32
2021-02-23 SPI working better now -> changed CS into a second synchronization signal -> use SPI polling instead of DMA on STM32 side
2021-02-23 Top level file missing from previous commit
2021-02-25 SPI pins mapped correctly in .qsf file. Quartus design regeneration.
2021-03-03 Fixed "build both firmwares" command in mk.bat
2021-03-18 Default boot ROM temporarily changed to WascaLoader
2021-03-18 Don't calculate CRC of the ROM after loading it. (this was just here for debug purpose)
2021-03-30 Increasing buffered SPI frequency (works on 3 out of 4 boards)
2021-06-06 Added API to test SPI communication (Implementation on STM32 and MAX10 sides will arrive soon)
2021-06-07 Descriptor update (does not work, BSODs the system, do not load)
2021-06-08 Device descriptor update
2021-06-08 Removing CDC, adding blaster (unfinished)
2021-06-14 mcu_blaster project removed
2021-06-15 Preparing actual play finctions (unfinished)
2021-06-19 Preparing actual play finctions (finished but untested)
2021-07-02 SVF player works (MAX10 firmware is integrated into STM32 player firmware)
2021-07-02 Minor cleanup
2021-07-11 Read settings from file on SD card (tested 80%) Allow cartridge configuration from settings file on SD card (tested 10%) Write log messages on SD card (tested 90%) Output logs to USB CDC (not tested)
2021-07-13 Board 1.5 , STM-to-MAX JTAG detached from UART
2021-07-18 Set SD card file time stamp from firmware build date (This will be improved to use real time when API with Saturn will be added)
2021-07-18 Allow to write logs into several files on SD card (Main interest is to keep previous log files after a power off/on)
2021-07-22 Cosmetic refactoring of backup RAM/boot ROM module (unified naming + full re-initialization of globals on STM32 startup)
2021-07-23 Mode setup logs to SD card + other code cleanup * Code review and logging on STM32 side and testing everything together shall be done on next week. * Sniffer incorrectly reports previous access ? For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
2021-08-01 Update settings file template (BTW, settings module is currently tweaked to not load settings from SD card, because it's boring to remove/insert it each time I want to tune settings)
2021-08-01 Throw error message when SPI communication failed on STM32 side Everything works well on my DE10-lite board, but not on my Wasca-compatible board. Errors don't happen on the former because it uses ha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
2021-08-01 Output some more logs from MAX 10 around backup memory access + Use "normal" log output function (which sends messages to STM32) instead of only sending to UART + Wait a bit (0.3 sec) on startup to b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
2021-08-05 Adding 4-speed SPI transmission into FPGA
2021-08-11 Fixed typo in settings file
2021-08-11 Changing wasca_mode among with REG_MODE. Delaying sniffer FIFO output (blind fix attempt).
2021-08-24 Removed old/slow single SPI transfer function (in order to prepare faster streaming of backup memory data to SD card)
2021-09-08 More log output during backup memory access
2021-11-09 SODIMM 200 connector
2022-01-12 SODIMM based board (preliminary work)
2022-01-21 Signaltap removed (it was affecting performance).
2022-01-21 Updating player with a new bitstream
2022-02-16 Don't load STM32 internal ROM when ROM ID is set to zero
2022-02-19 Bufferize backup memory access from FIFO to SDRAM, and write to SD card when FIFO is empty (untested) (Goal : allow safe writing of large save data files)
2022-02-20 Blink LED when setting up mode and flash it when syncing backup memory data to SD card (So far, the continuously blinking, even if nothing special was happening)
2022-03-02 Burst 2, caching previous read, always stopping burst at write. Fast reaction to read pulse (breaks something)
2022-03-08 Repairs and optimizations, speed down to 100 MHz
2022-03-11 BOM generated. Crystal value updated.
2022-03-18 NIos mapper control
2022-03-21 SFV player update
2022-03-26 Further cleanup
2022-03-30 Reroute complete, cleanup pending.
2022-04-04 Big SD connector
2022-04-06 Test points
2022-04-14 Logo update
2023-09-17 Migrating to Kicad 7
2023-09-17 Adding HyperRAM as an alternative for SDRAM
2023-09-18 Gerbers update, version 1.7
2023-09-21 Lattice blinky test
2023-09-22 Changing UART baudrate to 115200
2023-09-25 Extending SOC RAM to 64KB, simple memory test
2023-10-07 SD core is up in sim. Fails to init because the card sim model was not added yet.
2023-10-20 SD card works in simulation
2023-10-25 Slowing CPU down to 25MHz
2023-10-25 SD card is readable on hardware (data is scrambled, reason unknown)
2024-12-25 Adding fatfs, sd core checks
2024-12-30 Switching to Zipcpu SDIO core, sector reading works
2026-03-14 File listing
2026-03-26 SDRAM core (unfinished)
2026-04-01 Pushing ram into own module, reducing size to 80kb, speed is up to 90 mhz
2026-04-01 Overall optimization, RAM down to 64K, timing is still under 80MHz
2026-04-02 Dividing CPU and SDRAM domains, using 40 and 67 MHz respectively atm
2026-04-02 SDRAM tests, 67/40/25 MHz clocks
2026-04-04 removing SDRAM timing violations
2026-04-06 Clocks at 133/50/25
2026-04-07 Enabling parallel refine for pnr
2026-04-07 Full SDRAM test, parametrizing untill pass
2026-04-07 Adding 2nd sdram port
2026-04-08 Second SDRAM (timings fail atm)
2026-04-08 Optimization ,quick test report
2026-04-09 DQM doubling for SDRAM2
2026-04-10 Timing for SDRAM1, SDRAM2 not working yet
2026-04-11 Debugging SDRAM2
2026-04-20 Complete SDRAM + SDRAM2 test
2026-04-21 Storing bootstrap in SDRAM1
2026-04-22 CS0 and CS1 fix
2026-04-24 Enabling quick SDRAM1+2 tests. Dividing Abus and Wishbone read access latches
2026-04-25 Restoring 133/50/25 MHz
2026-05-03 CS1 rework, using ESP32 lines for debug
2026-05-04 Long DQ output for both ABUS and Wishbone over CS0
2026-05-05 Debugging fatfs
2026-05-06 Registers work now (after some soldering)
2026-05-08 Menu advertisement & preparing (unfinished)
2026-05-08 Software updates, backup selection in menu works now
2026-05-09 Sniffer-based blinking for Heart of Darkness
2026-05-10 Migrating to Kicad 10
2026-05-10 Set speedgrade to 6. RAM modes fix
2026-05-10 Adding FPGA+power supplies
2026-05-12 Cleanup. 1M/2M/4M backup syncing.
2026-05-14 Move submodule
2026-05-14 README update
2026-05-18 Board rerouting
2026-05-20 Resizing RP2040 drive (incomplete)
2026-05-20 Cleanup gerber products
2026-05-20 Writing to SPI flash in rp2040 bootloader (untested)
2026-05-21 Moving RP2040 to front to simplify 2-stage assembly (front at fab, back manually).
2026-05-22 Board 1.8 production
2026-05-22 Allowing mode reselection by switching to mode 0.
2026-05-22 ESP32 blink project
2026-05-24 Moving signature and swreg registers from logic to SDRAM
2026-05-24 Filesystem implementation (unfinished)
2026-05-25 Negedge wires cleanup. Extra latch for abus reg writes.
2026-05-25 Adding firmware project (to be loaded dynamically from SD by bootstrap)
2026-05-25 FPGA loading in QSPI mode, faster clock.
2026-05-25 filesystem complete but untested
2026-05-26 remove irrelevant comments
2026-05-26 Commander dummy gui
2026-05-27 Dir close crash fix
2026-05-28 Cart not detected message
2026-05-28 Somehow fatfs access fails without these delays. Should i wait for the SD core?
2026-06-01 Move fpga firmware for modular prototype version to a different folder
2026-06-01 Updating pinout for board 1.8
2026-06-01 Pre-filling panels file lists (unfinished)
2026-06-02 Cursor movement (not optimized yet)
2026-06-04 Syncing prototype sources
2026-06-04 Bootstrap cleanup, fallback rom message update
2026-06-04 Copying file from panel to panel
2026-06-07 Replies linting
2026-06-08 Restoring SDRAM test in both bootstrap and firmware
2026-06-08 16-bit bus for SDRAM2 (clock phase shift still necessary)
2026-06-08 Small board updates
2026-06-11 Oscillator update for easier handsoldering
2026-06-12 List command
2026-06-13 Read command
2026-06-13 Speedup, removing printf debug in PicoRV code
2026-06-13 Removing yaul CS0() macro from wascafs.c
2026-06-24 Backup sync fix.
2026-06-25 Superfloppy support
2026-06-26 Switching fpga updater's own firmware load to SPI x1 mode
2026-06-28 I2S test
2026-06-29 Memtest add. Increase clock to 141 MHz to match CS0 budget at 2 waitstates / 26.8 Mhz
2026-06-29 Folder rename
